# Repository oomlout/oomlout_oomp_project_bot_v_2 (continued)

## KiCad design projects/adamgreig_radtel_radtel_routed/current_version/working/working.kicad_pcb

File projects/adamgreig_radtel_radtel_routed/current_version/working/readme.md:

# radtel
 
## summary 
* id: adamgreig_radtel_radtel_routed
* user: adamgreig
* name: radtel
* board: radtel_routed
* repo: https://github.com/adamgreig/radtel
* src_file_repo_kicad_pcb: pcb/radtel_routed.kicad_pcb
* src_file_repo_kicad_pcb_link: https://github.com/adamgreig/radtel/tree/master/pcb/radtel_routed.kicad_pcb

* src_file_repo_sch: 
* src_file_repo_sch_link: https://github.com/adamgreig/radtel/tree/master/
* full details link: https://github.com/oomlout/oomlout_oomp_project_bot_v_2/tree/main/projects/adamgreig_radtel_radtel_routed/current_version/working  

## pcb  

[board (pdf)](working.pdf)  

## working_bom
| Id | Designator | Footprint | Quantity | Designation | Supplier and ref |  | None | 
| --- | --- | --- | --- | --- | --- | --- | --- | 
| 1 | C1,C2,C5,C10 | C0603 | 4 | 1Âµ |  |  | [''] | 
| 2 | C3 | C0603 | 1 | 1n |  |  | [''] | 
| 3 | C4 | C0603 | 1 | 3pF |  |  | [''] | 
| 4 | C6,C11,C12,C20 | C0603 | 4 | 100n |  |  | [''] | 
| 5 | C7 | C0603 | 1 | 1pF |  |  | [''] | 
| 6 | C8,C9 | C0603 | 2 | 10Âµ |  |  | [''] | 
| 7 | C13 | C0603 | 1 | 10n |  |  | [''] | 
| 8 | C14 | C0603 | 1 | 47pF |  |  | [''] | 
| 9 | C15 | C0603 | 1 | 5.1pF |  |  | [''] | 
| 10 | C16 | C0603 | 1 | 3.9pF |  |  | [''] | 
| 11 | C17,C19,C21,C22 | C0603 | 4 | 11p |  |  | [''] | 
| 12 | C18 | C0603 | 1 | 100p |  |  | [''] | 
| 13 | D1,D2,D3,D4,D5,D6,D7,D8 | R0603 | 8 | CGA0402MLC-12G |  |  | [''] | 
| 14 | D9,D11 | LED0603 | 2 | GREEN |  |  | [''] | 
| 15 | D10 | LED0603 | 1 | RED |  |  | [''] | 
| 16 | IC2 | Si4460 | 1 | Si4460 |  |  | [''] | 
| 17 | IC3 | LQFP48 | 1 | STM32F072CBT6 |  |  | [''] | 
| 18 | L1 | L0603 | 1 | 20nH |  |  | [''] | 
| 19 | L2 | L0603 | 1 | 24nH |  |  | [''] | 
| 20 | L3 | L0603 | 1 | 18nH |  |  | [''] | 
| 21 | L4 | L0603 | 1 | 13nH |  |  | [''] | 
| 22 | L5 | L0603 | 1 | 120nH |  |  | [''] | 
| 23 | P1 | S02B-PASK-2 | 1 | PWR |  |  | [''] | 
| 24 | P2 | S04B-PASK-2 | 1 | UART |  |  | [''] | 
| 25 | P3 | USB3065 | 1 | USB_OTG |  |  | [''] | 
| 26 | P4 | FTSH-105-01-F-D-K | 1 | SWD |  |  | [''] | 
| 27 | P5 | WHIPANT | 1 | ANTENNA |  |  | [''] | 
| 28 | R1,R2,R3 | R0603 | 3 | 1k |  |  | [''] | 
| 29 | Y1 | XTAL50x32 | 1 | 26MHz |  |  | [''] | 
| 30 | Y2 | XTAL50x32 | 1 | 8MHz |  |  | [''] | 
| 31 | IC1 | MSOP8 | 1 | ADP3335 |  |  | [''] | 
| 32 | M3_MOUNT,M3_MOUNT | M3_MOUNT | 2 | VAL** |  |  | [''] |

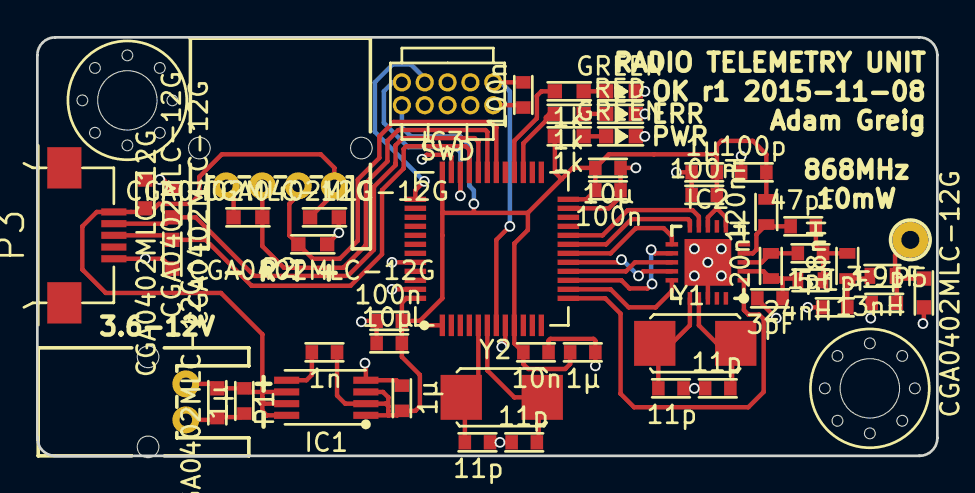
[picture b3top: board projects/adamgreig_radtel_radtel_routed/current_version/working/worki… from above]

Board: 2 copper layers, 50.0 x 23.2 mm, 53 parts (0 on the bottom side), 34 nets.

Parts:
C1, C2, C5, C10: 1µ; C0603
C3: 1n; C0603
C4: 3pF; C0603
C6, C11, C12, C20: 100n; C0603
C7: 1pF; C0603
C8, C9: 10µ; C0603
C13: 10n; C0603
C14: 47pF; C0603
C15: 5.1pF; C0603
C16: 3.9pF; C0603
C17, C19, C21, C22: 11p; C0603
C18: 100p; C0603
D1, D2, D3, D4, D5, D6, D7, D8: CGA0402MLC-12G; R0603
D9, D11: GREEN; LED0603
D10: RED; LED0603
IC1: ADP3335; MSOP8
IC2: Si4460
IC3: STM32F072CBT6; LQFP48
L1: 20nH; L0603
L2: 24nH; L0603
L3: 18nH; L0603
L4: 13nH; L0603
L5: 120nH; L0603
M3_MOUNT, M3_MOUNT#2: VAL**; M3_MOUNT
P1: PWR; S02B-PASK-2
P2: UART; S04B-PASK-2
P3: USB_OTG; USB3065
P4: SWD; FTSH-105-01-F-D-K
P5: ANTENNA; WHIPANT
R1, R2, R3: 1k; R0603
Y1: 26MHz; XTAL50x32
Y2: 8MHz; XTAL50x32

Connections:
+3V3: C2.1, C3.2, C5.1, C6.1, C8.1, C9.1, C10.1, C11.1, C12.1, C13.1, C18.1, IC1.1, IC1.2, IC1.3, IC2.6, IC2.8, IC3.1, IC3.9, IC3.24, IC3.36, IC3.48, L5.1, P4.1, R2.1
+BATT: C1.1, D1.2, D4.1, D7.1, IC1.6, IC1.7, IC1.8, P1.2, P2.4, P3.1
/SI_GPIO0: IC2.9, IC3.20
/SI_GPIO1: IC2.10, IC3.19
/SI_MISO: IC2.13, IC3.16
/SI_MOSI: IC2.14, IC3.17
/SI_NIRQ: IC2.11, IC3.18
/SI_NSS: IC2.15, IC3.14
/SI_SCK: IC2.12, IC3.15
/SI_SDN: IC2.1, IC3.13
/SWCLK: IC3.37, P4.4
/SWDIO: IC3.34, P4.2
/UART_RX: D2.1, IC3.31, P2.2
/UART_TX: D3.1, IC3.30, P2.3
/USB_DM: D6.1, IC3.32, P3.2
/USB_DP: D5.1, IC3.33, P3.3
/nRST: C20.1, IC3.7, P4.10
GND: C1.2, C2.2, C4.1, C5.2, C6.2, C8.2, C9.2, C10.2, C11.2, C12.2, C13.2, C15.2, C16.2, C17.2, C18.2, C19.2, C20.2, C21.2, C22.2, D1.1, D2.2, D3.2, D4.2, D5.2, D6.2, D7.2, D8.1, D9.1, D10.1, D11.1, IC1.4, IC2.18, IC2.PAD, IC3.8, IC3.23, IC3.35, IC3.44, IC3.47, P1.1, P2.1, P3.5, P4.3, P4.5, P4.9
unnamed: C3.1, IC1.5
unnamed: C4.2, IC2.2, L1.2, L2.1
unnamed: C7.1, IC2.3, L1.1
unnamed: C7.2, C14.1, L2.2, L3.1
unnamed: C14.2, IC2.4, L5.2
unnamed: C15.1, L3.2, L4.1
unnamed: C16.1, D8.2, L4.2, P5.1
unnamed: C17.1, IC2.16, Y1.1
unnamed: C19.1, IC2.17, Y1.2
unnamed: C21.1, IC3.5, Y2.1
unnamed: C22.1, IC3.6, Y2.2
unnamed: D9.2, R3.2
unnamed: D10.2, R1.2
unnamed: D11.2, R2.2
unnamed: IC3.27, R1.1
unnamed: IC3.28, R3.1

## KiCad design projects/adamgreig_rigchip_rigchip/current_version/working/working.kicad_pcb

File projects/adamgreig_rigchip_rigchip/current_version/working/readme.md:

# rigchip
 
## summary 
* id: adamgreig_rigchip_rigchip
* user: adamgreig
* name: rigchip
* board: rigchip
* repo: https://github.com/adamgreig/rigchip
* src_file_repo_kicad_pcb: pcb/rigchip.kicad_pcb
* src_file_repo_kicad_pcb_link: https://github.com/adamgreig/rigchip/tree/master/pcb/rigchip.kicad_pcb

* src_file_repo_sch: pcb/rigchip.sch
* src_file_repo_sch_link: https://github.com/adamgreig/rigchip/tree/master/pcb/rigchip.sch
* full details link: https://github.com/oomlout/oomlout_oomp_project_bot_v_2/tree/main/projects/adamgreig_rigchip_rigchip/current_version/working  

## schematic  
  
[schematic (pdf)](working_schematic.pdf) 

## pcb  

[board (pdf)](working.pdf)  

## working_bom
| Id | Designator | Footprint | Quantity | Designation | Supplier and ref |  | None | 
| --- | --- | --- | --- | --- | --- | --- | --- | 
| 1 | C1,C4,C5,C6,C7 | 0603 | 5 | 100n |  |  | [''] | 
| 2 | C2,C3 | 1206 | 2 | 10Âµ |  |  | [''] | 
| 3 | D1,D2,D3,D4,D5,D6,D7 | 0402 | 7 | ESD_DIODE |  |  | [''] | 
| 4 | D8 | 0603-LED | 1 | GRN |  |  | [''] | 
| 5 | D9 | 0603-LED | 1 | RED |  |  | [''] | 
| 6 | IC1 | TSR1 | 1 | TSR1 |  |  | [''] | 
| 7 | IC2 | CHIPv1_0 | 1 | CHIPv1_0 |  |  | [''] | 
| 8 | J1 | S02B-PASK-2 | 1 | POWER |  |  | [''] | 
| 9 | J2 | S05B-PASK-2 | 1 | DATA |  |  | [''] | 
| 10 | J3 | S03B-PASK-2 | 1 | CONTROL |  |  | [''] | 
| 11 | L1 | TYS5040 | 1 | 6Âµ8 |  |  | [''] | 
| 12 | L2,L3,L4,L5,L6,L7 | 0603 | 6 | FB |  |  | [''] | 
| 13 | R1,R2,R3,R4 | 0603 | 4 | 1k |  |  | [''] | 
| 14 | IC3,IC4,IC5 | SOT-23-5 | 3 | SN74LVC1G07 |  |  | [''] | 
| 15 | R5 | 0603 | 1 | 10k |  |  | [''] | 
| 16 | D10 | 0603-LED | 1 | ~ |  |  | [''] | 

## bom_schematic
| Ref | Qnty | Value | Cmp name | Footprint | Description | Vendor | DNP | 
| --- | --- | --- | --- | --- | --- | --- | --- | 
| C1, C4, C5, C6, C7 | 5 | 100n | C | agg:0603 |  |  |  | 
| C2, C3 | 2 | 10Âµ | C | agg:1206 |  |  |  | 
| D1, D2, D3, D4, D5, D6, D7 | 7 | ESD_DIODE | ESD_DIODE | agg:0402 |  |  |  | 
| D8 | 1 | GRN | LED | agg:0603-LED |  |  |  | 
| D9 | 1 | RED | LED | agg:0603-LED |  |  |  | 
| D10 | 1 | ~ | SCHOTTKY | agg:0603-LED |  |  |  | 
| IC1 | 1 | TSR1 | TSR1 | agg:TSR1 |  |  |  | 
| IC2 | 1 | CHIPv1_0 | CHIPv1_0 | agg:CHIPv1_0 |  |  |  | 
| IC3, IC4, IC5 | 3 | SN74LVC1G07 | SN74LVC1G07 | agg:SOT-23-5 |  |  |  | 
| J1 | 1 | POWER | CONN_01x02 | agg:S02B-PASK-2 |  |  |  | 
| J2 | 1 | DATA | CONN_01x05 | agg:S05B-PASK-2 |  |  |  | 
| J3 | 1 | CONTROL | CONN_01x03 | agg:S03B-PASK-2 |  |  |  | 
| L1 | 1 | 6Âµ8 | L | agg:TYS5040 |  |  |  | 
| L2, L3, L4, L5, L6, L7 | 6 | FB | L | agg:0603 |  |  |  | 
| R1, R2, R3, R4 | 4 | 1k | R | agg:0603 |  |  |  | 
| R5 | 1 | 10k | R | agg:0603 |  |  |  | 
| X1, X2 | 2 | CONN | PART |  |  |  |  |

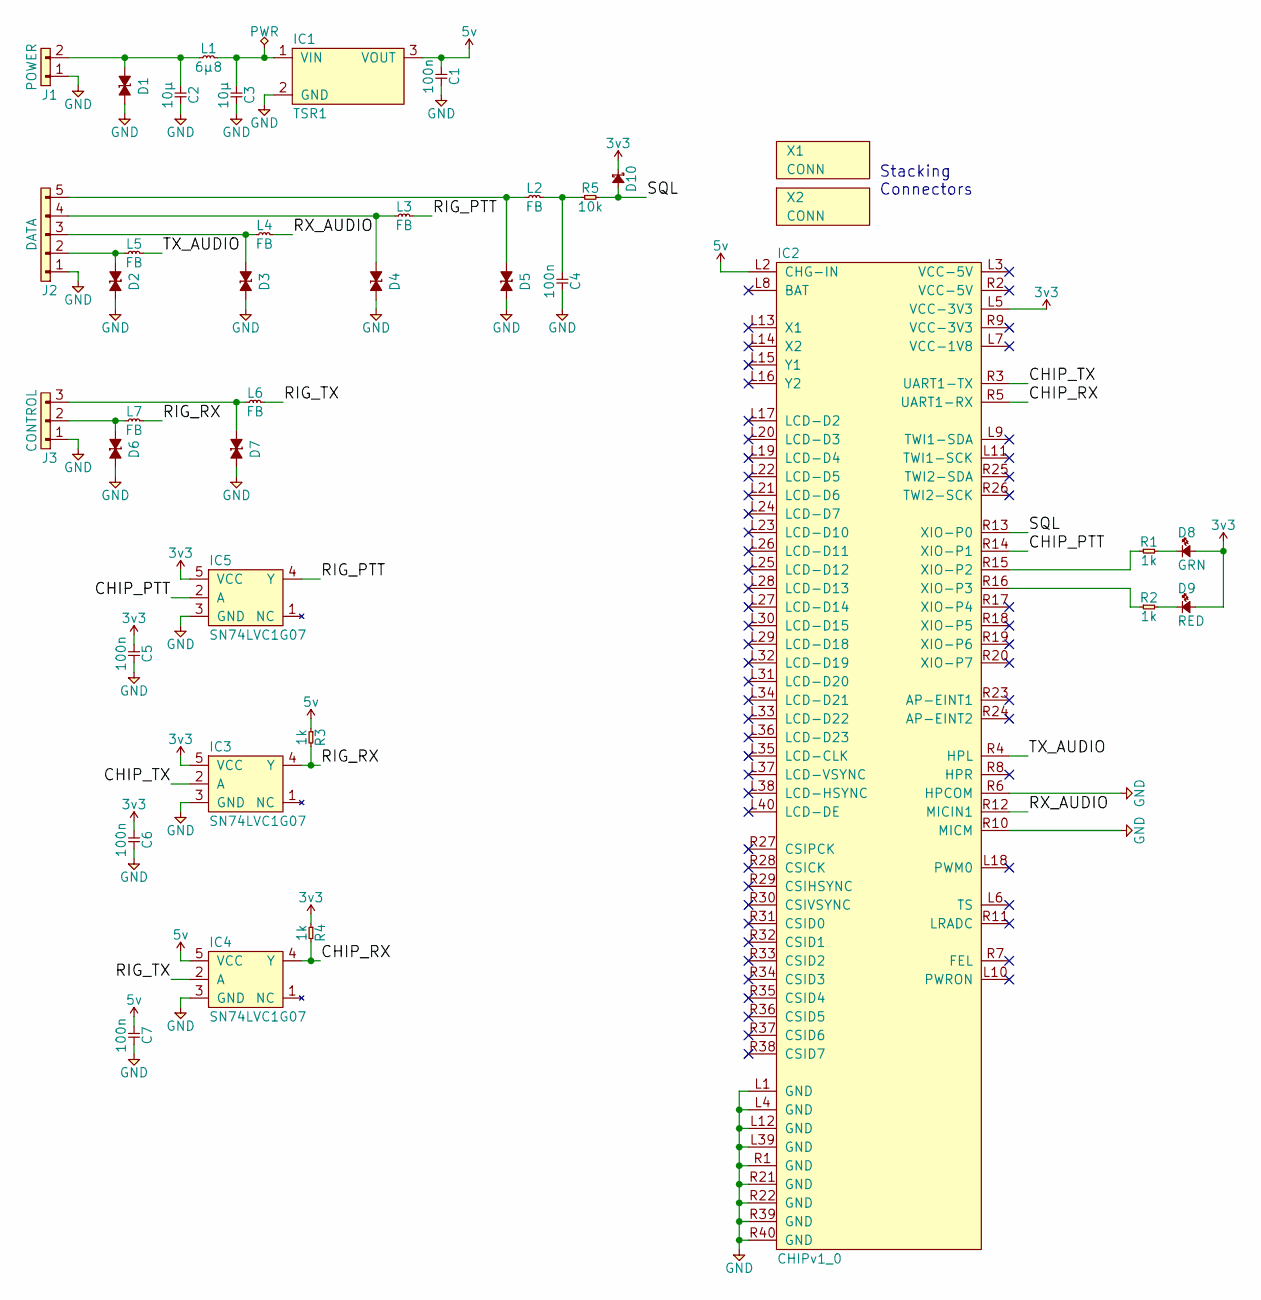
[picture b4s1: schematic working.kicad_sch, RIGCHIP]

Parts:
C1, C4, C5, C6, C7: 100n; 0603; Farnell 2496834
C2, C3: 10µ; 1206; Farnell 2211092
D1, D2, D3, D4, D5, D6, D7: ESD_DIODE; 0402; Farnell 2368169
D8: GRN; 0603-LED; Farnell 2290328
D9: RED; 0603-LED; Farnell 2290329
D10: 0603-LED; Farnell 2341897
IC1: TSR1; Farnell 1696320
IC2: CHIPv1_0
IC3, IC4, IC5: SN74LVC1G07; SOT-23-5; Farnell 1102969
J1: POWER; S02B-PASK-2; Farnell 1830747
J2: DATA; S05B-PASK-2; Farnell 1830750
J3: CONTROL; S03B-PASK-2; Farnell 1830748
L1: 6µ8; TYS5040; Farnell 2292530
L2, L3, L4, L5, L6, L7: FB; 0603; Farnell 1463451
R1, R2, R3, R4: 1k; 0603; Farnell 9238484
R5: 10k; 0603; Farnell 9238603
X1, X2: CONN; Farnell 1569230

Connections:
3v3: C5.1, C6.1, D8.2, D9.2, D10.1, IC2.L5 (VCC-3V3), IC3.5 (VCC), IC5.5 (VCC), R4.1
5v: C1.1, C7.1, IC1.3 (VOUT), IC2.L2 (CHG-IN), IC4.5 (VCC), R3.1
/CHIP_PTT: IC2.R14 (XIO-P1), IC5.2 (A)
/CHIP_RX: IC2.R5 (UART1-RX), IC4.4 (Y), R4.2
/CHIP_TX: IC2.R3 (UART1-TX), IC3.2 (A)
/RIG_PTT: IC5.4 (Y), L3.2
/RIG_RX: IC3.4 (Y), L7.2, R3.2
/RIG_TX: IC4.2 (A), L6.2
/RX_AUDIO: IC2.R12 (MICIN1), L4.2
/SQL: D10.2, IC2.R13 (XIO-P0), R5.2
/TX_AUDIO: IC2.R4 (HPL), L5.2
GND: C1.2, C2.2, C3.2, C4.2, C5.2, C6.2, C7.2, D1.2, D2.2, D3.2, D4.2, D5.2, D6.2, D7.2, IC1.2 (GND), IC2.L1 (GND), IC2.L4 (GND), IC2.L12 (GND), IC2.L39 (GND), IC2.R1 (GND), IC2.R6 (HPCOM), IC2.R10 (MICM), IC2.R21 (GND), IC2.R22 (GND), IC2.R39 (GND), IC2.R40 (GND), IC3.3 (GND), IC4.3 (GND), IC5.3 (GND), J1.1, J2.1, J3.1
unnamed: C2.1, D1.1, J1.2, L1.1
unnamed: C3.1, IC1.1 (VIN), L1.2
unnamed: C4.1, L2.2, R5.1
unnamed: D2.1, J2.2, L5.1
unnamed: D3.1, J2.3, L4.1
unnamed: D4.1, J2.4, L3.1
unnamed: D5.1, J2.5, L2.1
unnamed: D6.1, J3.2, L7.1
unnamed: D7.1, J3.3, L6.1
unnamed: D8.1, R1.2
unnamed: D9.1, R2.2
unnamed: IC2.R15 (XIO-P2), R1.1
unnamed: IC2.R16 (XIO-P3), R2.1

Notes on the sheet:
Stacking Connectors

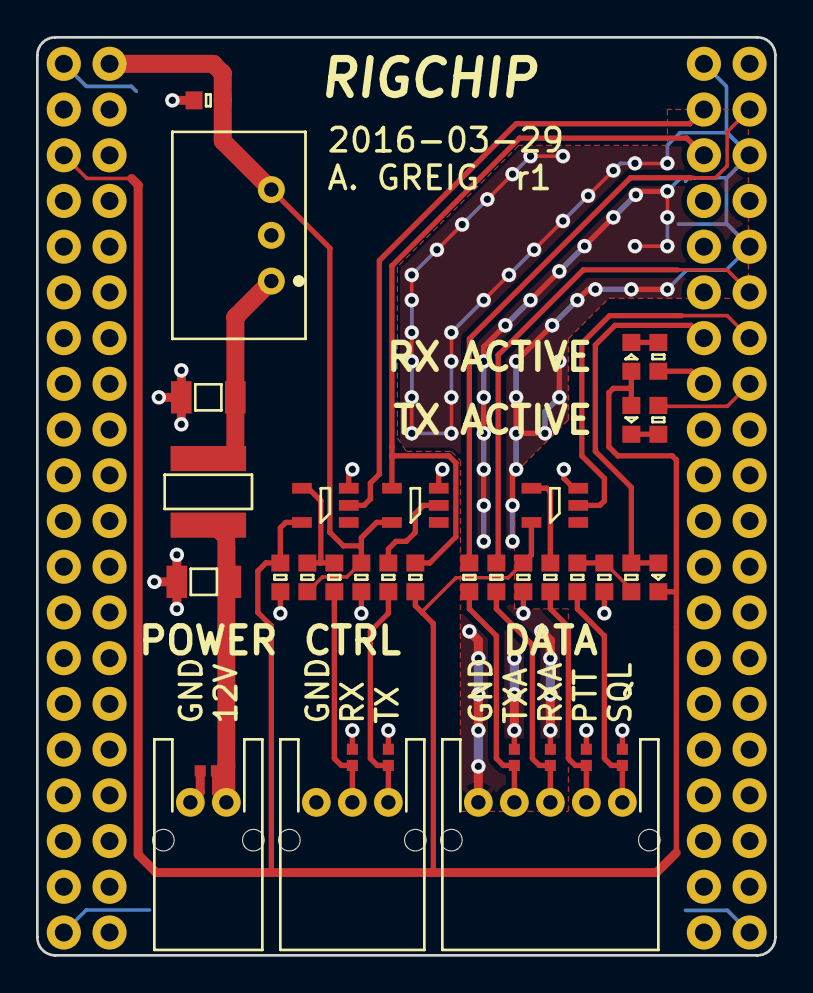
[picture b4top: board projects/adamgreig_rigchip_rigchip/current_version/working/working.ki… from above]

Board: 2 copper layers, 41.0 x 51.0 mm, 37 parts (0 on the bottom side), 25 nets.

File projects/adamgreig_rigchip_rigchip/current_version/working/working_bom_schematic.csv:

"Source:","C:\gh\oomlout_oomp_project_bot_v_2\projects\adamgreig_rigchip_rigchip\current_version\working\working.kicad_sch"
"Date:","18/09/2023 14:44:28"
"Tool:","Eeschema 7.0.6"
"Generator:","C:/Program Files/KiCad/7.0/bin/scripting/plugins/bom_csv_grouped_by_value_with_fp.py"
"Component Count:","39"
"Ref","Qnty","Value","Cmp name","Footprint","Description","Vendor","DNP"
"C1, C4, C5, C6, C7","5","100n","C","agg:0603","","",""
"C2, C3","2","10µ","C","agg:1206","","",""
"D1, D2, D3, D4, D5, D6, D7","7","ESD_DIODE","ESD_DIODE","agg:0402","","",""
"D8","1","GRN","LED","agg:0603-LED","","",""
"D9","1","RED","LED","agg:0603-LED","","",""
"D10","1","~","SCHOTTKY","agg:0603-LED","","",""
"IC1","1","TSR1","TSR1","agg:TSR1","","",""
"IC2","1","CHIPv1_0","CHIPv1_0","agg:CHIPv1_0","","",""
"IC3, IC4, IC5","3","SN74LVC1G07","SN74LVC1G07","agg:SOT-23-5","","",""
"J1","1","POWER","CONN_01x02","agg:S02B-PASK-2","","",""
"J2","1","DATA","CONN_01x05","agg:S05B-PASK-2","","",""
"J3","1","CONTROL","CONN_01x03","agg:S03B-PASK-2","","",""
"L1","1","6µ8","L","agg:TYS5040","","",""
"L2, L3, L4, L5, L6, L7","6","FB","L","agg:0603","","",""
"R1, R2, R3, R4","4","1k","R","agg:0603","","",""
"R5","1","10k","R","agg:0603","","",""
"X1, X2","2","CONN","PART","","","",""
